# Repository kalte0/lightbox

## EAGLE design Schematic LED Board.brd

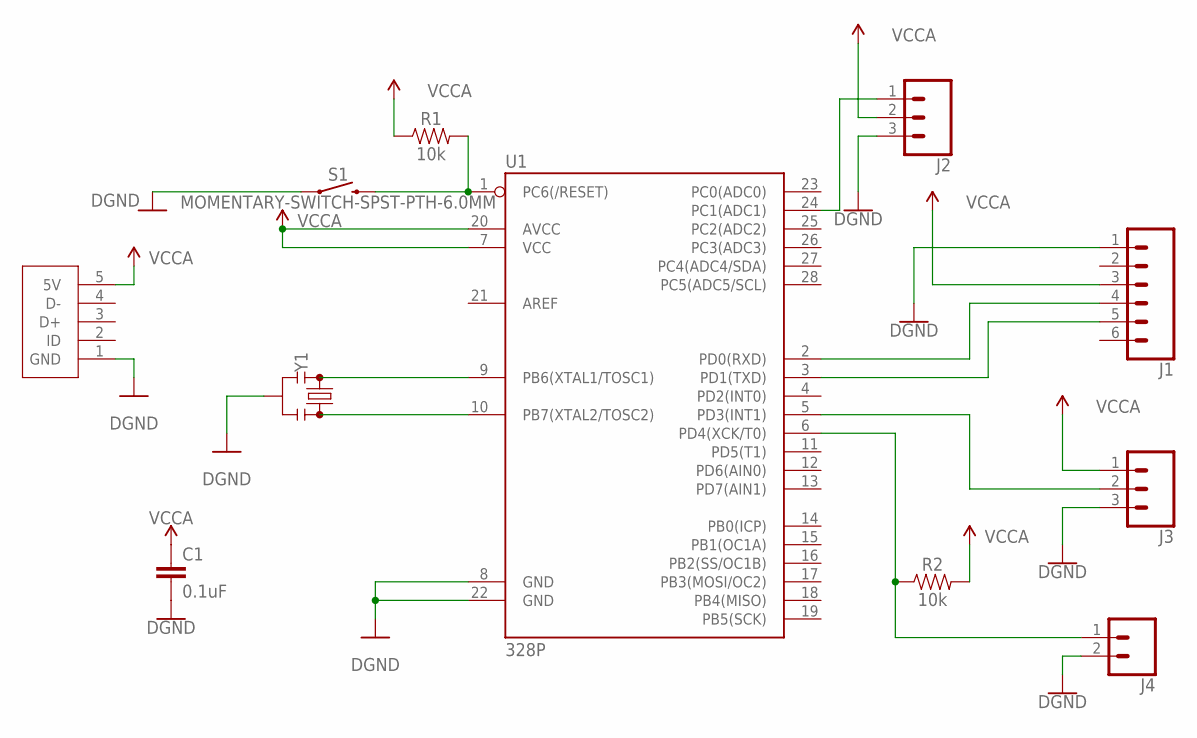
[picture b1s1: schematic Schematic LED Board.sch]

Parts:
C1: 0.1uF; CAP-PTH-SMALL-KIT
J1: CONN_06LONGPADS; 1X06_LONGPADS
J2, J3: CONN_03LONGPADS; 1X03_LONGPADS
J4: CONN_02PTH3; 1X02_LONGPADS
R1, R2: 10k; AXIAL-0.3
S1: MOMENTARY-SWITCH-SPST-PTH-6.0MM; TACTILE_SWITCH_PTH_6.0MM
U1: 328P; DIP28
U$8: USBPOWER; 1X05_LONGPADS
Y1: RESONATORPTH-7.6X3.8; RESONATOR-PTH-7.6X3.8

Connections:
GND: C1.2, J1.1, J2.3, J3.3, J4.2, S1.1, U1.8 (GND), U1.22 (GND), U$8.1 (GND), Y1.2
unnamed: U1.9 (PB6(XTAL1/TOSC1)), Y1.1
unnamed: R1.P$2 (2), S1.3 (2), U1.1 (PC6(/RESET))
unnamed: U1.10 (PB7(XTAL2/TOSC2)), Y1.3
unnamed: J3.2, U1.5 (PD3(INT1))
unnamed: J1.4, U1.2 (PD0(RXD))
unnamed: J1.5, U1.3 (PD1(TXD))
unnamed: J2.1, U1.24 (PC1(ADC1))
unnamed: J4.1, R2.P$1 (1), U1.6 (PD4(XCK/T0))
VCCA: C1.1, J1.3, J2.2, J3.1, R1.P$1 (1), R2.P$2 (2), U1.7 (VCC), U1.20 (AVCC), U$8.5 (5V)

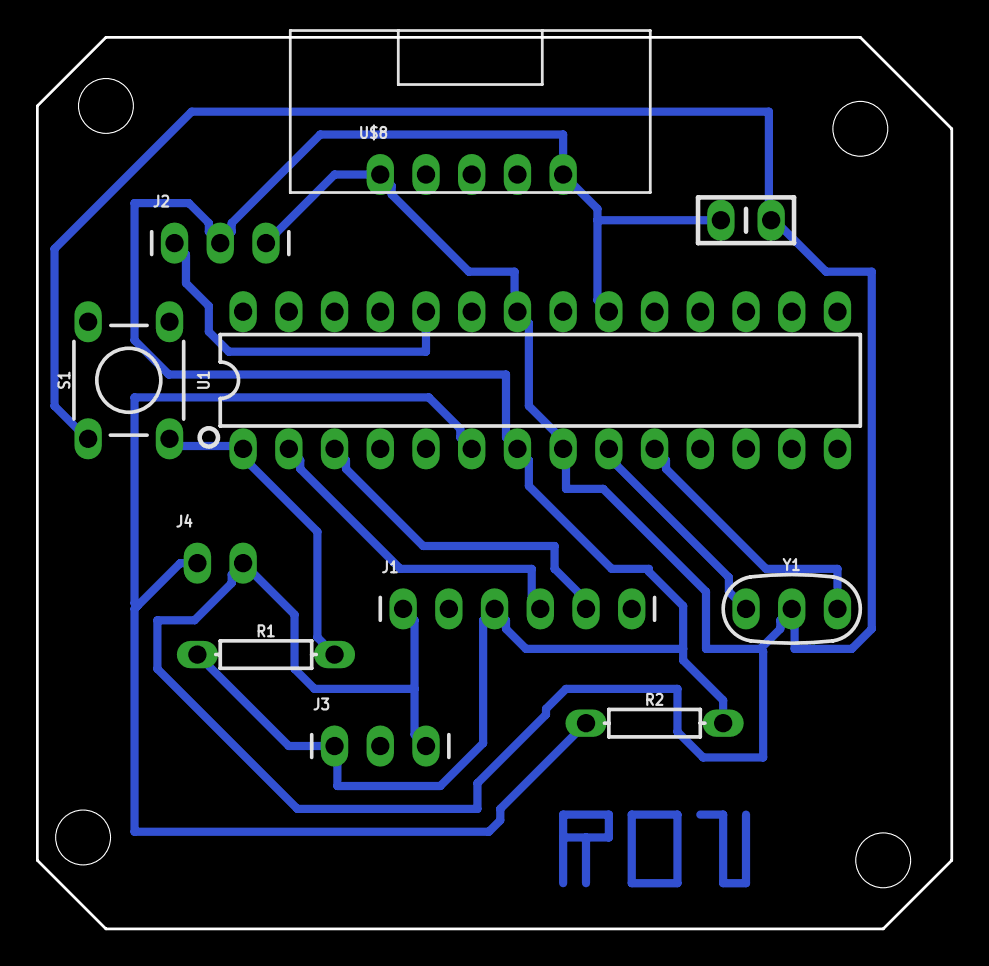
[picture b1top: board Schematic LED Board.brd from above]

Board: 2 copper layers, 50.8 x 49.5 mm, 11 parts (0 on the bottom side), 10 nets.

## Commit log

2019-01-22 Info Dump
    The project is completely finished, but I'm putting the code, a picture of the board, and dxf files of each side into the repository.
2019-01-22 here are the Eagle Files
2019-01-22 Added Price sheet
2019-01-30 Added pictures and video
    Pictures of the completed project (proof I actually did it I guess.

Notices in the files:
parts and their libraries:
SparkFun-PowerSymbols: Licensing: Creative Commons ShareAlike 4.0 International - https://creativecommons.org/licenses/by-sa/4.0
